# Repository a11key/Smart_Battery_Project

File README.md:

# Smart_Battery_Project
# Репозиторий проекта "УМНЫЙ АКБ для БАС"

## Министерство науки и высшего образования Российской Федерации  
### ФЕДЕРАЛЬНОЕ ГОСУДАРСТВЕННОЕ АВТОНОМНОЕ ОБРАЗОВАТЕЛЬНОЕ УЧРЕЖДЕНИЕ ВЫСШЕГО ОБРАЗОВАНИЯ  
### «МОСКОВСКИЙ ФИЗИКО-ТЕХНИЧЕСКИЙ ИНСТИТУТ (НАЦИОНАЛЬНЫЙ ИССЛЕДОВАТЕЛЬСКИЙ УНИВЕРСИТЕТ)» (МФТИ, Физтех)

---

## Описание проекта

**Название проекта:** УМНЫЙ АКБ для БАС

**Работу выполнили:**  
- Мацкевич Алексей
- Салахов Камиль 
- Васильев Андрей 

**Дата:** Долгопрудный, 19.12.2024

### Аннотация
Проект направлен на разработку аккумуляторного модуля для беспилотной авиационной системы (БАС), который позволяет передавать параметры АКБ (температуру, напряжение, ток заряда/разряда) на внешнее устройство.

### Цель и задачи
**Цель:** Создать модуль для БАС с возможностью беспроводной связи с внешним устройством для мониторинга параметров аккумуляторов в реальном времени.

**Задачи:**
1. Спроектировать корпус АКБ, позволяющий интегрировать плату для мониторинга параметров и передачи данных на внешнее устройство.
2. Спроектировать плату с датчиками для фиксации состояния АКБ.
3. Разработать программное обеспечение, которое сможет регистрировать данные в режиме реального времени или записывать их в память.

### Использованное оборудование
- 2 платформы Arduino Nano
- 2 высокоточных датчика температуры (±0,25 °C) MCP9808
- LM2596 DC-DC Module (встраиваемый стабилизатор напряжения)
- Датчик Холла ACS712
- 2 радиомодуля NRF24L01 PA LNA
- 3 резистора (10 кОм)

### Ход создания
1. Спроектирована схема основного и принимающего модулей.

2. Попытка распечатать плату под схему. Из-за неудачных попыток создания было принято решение спаять компоненты схемы проводами.

3. Проектирование соединения для соединения АКБ с модулем. Корпус из пластика, распечатанный на 3D-принтере, был бы громоздким и тяжелым, поэтому было принято решение скреплять плату более простым и эффективным способом.

4. Разработано приложение, отображающее параметры, которые были приняты с модуля, прикрепленного к АКБ.

5. Подобраны провода, которые пригодны для использования с аккумулятором Li-Po Fullymax 30C.

### Результаты работы
Создан модуль, позволяющий считывать температуру, напряжение и ток заряда/разряда с АКБ и передавать эти параметры на внешнее устройство.

---

## Установка и использование
В процессе...

---

Для получения дополнительной информации или вопросов, пожалуйста, свяжитесь с авторами проекта.

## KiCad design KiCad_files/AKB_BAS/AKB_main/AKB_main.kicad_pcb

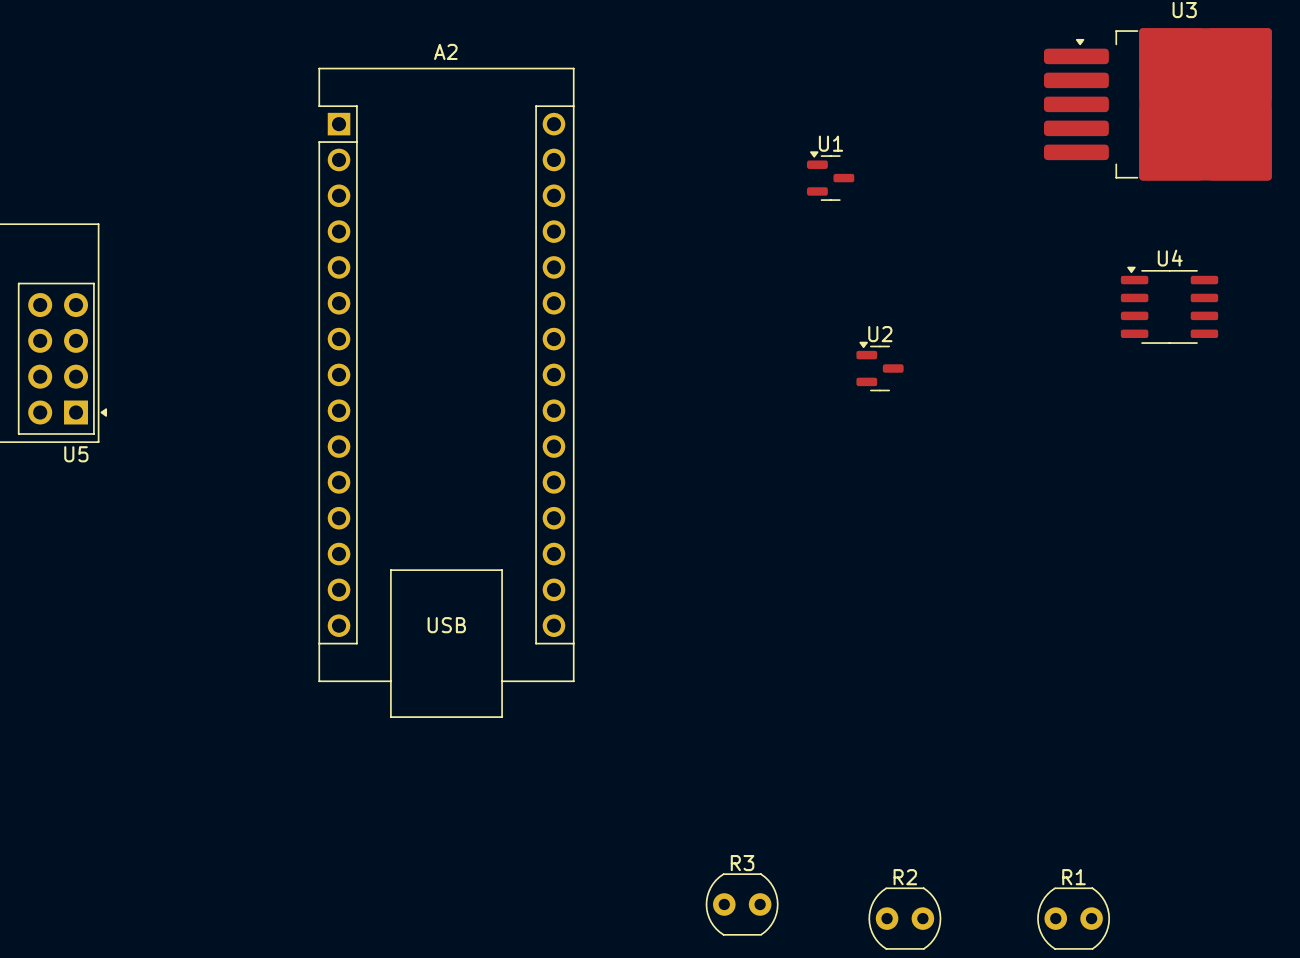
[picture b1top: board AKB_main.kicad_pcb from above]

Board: 2 copper layers, 9 parts (0 on the bottom side), 9 nets, no tracks yet.

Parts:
A2: Arduino_Nano_v3.x; Arduino_Nano
R1, R2, R3: R; R_LDR_4.9x4.2mm_P2.54mm_Vertical
U1, U2: MCP9808_MSOP; SOT-23
U3: LM2596S-12; TO-263-5_TabPin3
U4: ACS712xLCTR-30A; SOIC-8_3.9x4.9mm_P1.27mm
U5: NRF24L01_Breakout; nRF24L01_Breakout

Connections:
unnamed: A2.27 (+5V), U5.2 (VCC)
unnamed: A2.12 (D9), U5.3 (CE)
unnamed: A2.13 (D10), U5.4 (~CSN)
unnamed: A2.14 (D11), U5.6 (MOSI)
unnamed: A2.15 (D12), U5.7 (MISO)
unnamed: A2.16 (D13), U5.5 (SCK)
unnamed: U4.1 (IP+), U4.2 (IP+)
unnamed: U4.3 (IP-), U4.4 (IP-)
unnamed: A2.29 (GND), U5.1 (GND)

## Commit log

2024-12-18 Added operating code AKB_BAS.ino (with out antenna)
2024-12-20 added all files
2024-12-21 Modified documentation
